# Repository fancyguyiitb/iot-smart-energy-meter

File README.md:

<!-- DON'T MODIFY ANYTHING ABOVE -->
<!-- Modify from here -->

## Run it locally (no hardware needed)

The whole system runs on one machine. A **virtual meter board** stands in for the ADE9000 chip, the relays and the house wiring. The unmodified firmware talks to it through a hardware-abstraction layer.

```bash
python -m venv .venv
.venv/Scripts/activate            # Windows  (macOS/Linux: source .venv/bin/activate)
pip install -r requirements-dev.txt

python scripts/run_local.py       # add --gui for the meter's touchscreen UI
```

| Open | What it is |
|---|---|
| http://127.0.0.1:8000/app/ | Web app: live readings, energy use, analysis, power quality, remote control |
| http://127.0.0.1:9000/ | Virtual board: switch appliances, inject sags/outages/loose neutral/solar export, watch relays and ground truth |
| http://127.0.0.1:8000/docs | API reference |

On first start the launcher prints a one-time sign-up link that registers the meter to a new account. Run `python src/RPi/claim.py` for a fresh one.

```bash
python scripts/run_tests.py       # unit + regression tests (firmware and server)
python scripts/e2e_check.py       # end-to-end checks against the running stack
```

### How it fits together

```
 Virtual board (src/VirtualDevice)          Firmware (src/RPi)                    Server (src/Server)          Web app (src/WebApp)
 physics: grid, loads, faults   <-SPI-  api.py      sampler -> SQLite (WAL)    sync.py --HTTPS batches-->  /api/write-data
 emulated ADE9000 registers             sync.py     store-and-forward                                       SQLite (local) | InfluxDB (cloud)
 relay contacts on GPIO 17/27/22 <-GPIO- relay.py   <---------- WebSocket (device key) ------------>  /ws  <- /remote-control <- browser
                                        failure_log.py, app.py (Tk touchscreen)                         /auth, /api, /analytics -> browser
```

On the real Pi, set `VOLTIX_HAL=hardware` in `src/RPi/device.env` and the same firmware uses `spidev` and `RPi.GPIO`.

### Repository layout

| Path | Contents |
|---|---|
| `src/RPi/` | Meter firmware: sampler, sync, relay control, failure logger, touchscreen GUI, ADE9000 driver, `hal/` (real or virtual hardware) |
| `src/VirtualDevice/` | Virtual meter board: physical model, register-level ADE9000 emulation, control panel |
| `src/Server/` | FastAPI backend: auth, ingest, analytics, device WebSocket, `storage/` (SQLite or InfluxDB), `manage.py` |
| `src/WebApp/` | Browser client (reference client while the Flutter source is missing) |
| `src/Application/` | Flutter project scaffold (the Dart `lib/` was lost to a `.gitignore` rule, now fixed) |
| `scripts/` | `run_local.py`, `run_tests.py`, `e2e_check.py` |
| `tests/` | Firmware and server regression tests |
| `docs/BUGFIXES.md` | Open bugs, known limitations, and the feature backlog |
| `deploy/` | InfluxDB compose file for trying the cloud storage backend |
| `pcb/`, `3d_models/`, `reports/`, `others/`, `bom.xls` | Hardware design files and project reports |

---

# Project Overview

### Project Name: [IOT Enabled 3-Phase Power Quality and Energy Meter]()

### Team Number: [TUE-17]()

### Team Members

- [Saurabh Kumar](https://www.github.com/srbh001)
- [Aryan Tamboli](https://www.github.com/Aryan-Tamboli)
- [Ayush Gaur](https://www.github.com/gaurkama)
- [Cherish Jain](https://www.github.com/CJain2004)
- [Sarthak Niranjan](https://www.github.com/fancyguyiitb)

### Problem Statement and Solution

We developed an IoT-based 3-phase smart energy meter that enables users to monitor power parameters, analyze power quality, and remotely control the power supply. The system supports real-time data logging, mobile access, and predictive maintenance via harmonics analysis.  
For setup and usage instructions, refer to [Manual.md](Manual.md)..

#### Team & Contributions

Our team of 5 worked collaboratively across various components:

- PCB design and hardware integration for accurate signal acquisition
- App development for Android with real-time graphs and analytics
- Server-side APIs and cloud storage for historical data access
- GUI and control functionalities on Raspberry Pi
- Relay-based remote disconnection of supply

#### Key Learnings & Achievements

- Practical experience in embedded systems, IoT, and full-stack development
- Developed a complete system from hardware to cloud and mobile
- Built scalable architecture and an intuitive UI for energy monitoring

## 1. Source Code

### Application/

Flutter frontend for real-time monitoring and control. Contains Dart UI code (`lib/`), assets, platform-specific code, and Flutter config files.

### RPi/

Python scripts for data collection from ADE9000, local caching via SQLite, device control, syncing, and status tracking.

### Server/

FastAPI backend for authentication, data ingestion (InfluxDB), analytics, and WebSocket command handling. Includes API routes, config, and docs.

---

## Learning from Mistakes

### 1. UI Lag Due to Excessive Local Storage Data on Raspberry Pi

**Problem:**  
We encountered significant UI lag on the Raspberry Pi when the local storage accumulated large volumes of data. This led to delayed response times, particularly while switching between tabs, resulting in a poor user experience.

**Solution Implemented:**

- **Data Limitation:** We limited local data storage to only one day's worth of energy data to prevent database bloat and ensure smoother real-time operations.
- **Historical Data Handling:** For the "History" tab, we retained only a single representative energy data point from the previous day. This allowed for historical trend analysis with minimal storage overhead.
- **Improved UI Feedback:** A loading screen was introduced when switching tabs to:
  - Indicate the system is processing,
  - Discourage excessive button tapping,
  - Improve overall user satisfaction and interface intuitiveness.

**Outcome:**  
The optimizations resulted in a significantly more responsive and user-friendly interface with better resource management on the Raspberry Pi.

---

### 2. Power Backup System Failure

**Problem:**  
The power backup system failed to operate as intended during initial testing. Despite proper wiring and configuration, the battery did not charge, leading to a complete failure of backup functionality during power outages.

**Diagnosis and Root Cause:**  
After thorough inspection, we discovered that enclosing the circuitry between two tightly fitted acrylic sheets had introduced mechanical stress. This stress likely caused certain solder joints or connectors to either loosen or become overly compressed, ultimately disrupting the battery charging pathway.

**Solution Implemented:**

- **Mechanical Redesign:** We removed one of the acrylic sheets from the enclosure to relieve the internal stress and allow for natural ventilation and movement.
- **Post-Modification Testing:** After this adjustment, the charging system began functioning correctly, indicating that the issue was indeed related to physical strain affecting circuit integrity.

**Outcome:**  
Since this mechanical modification, the backup system has consistently charged without failure. This incident highlighted the critical importance of allowing tolerance for mechanical flexibility in compact hardware designs, especially when working with sensitive analog and power electronics.

---

## Future Scope

To further enhance the system’s functionality, usability, and sustainability, future contributors can explore the following improvements:

### 1. Sound Alerts for Power Failure

Implementing audio alerts during power failures can significantly improve user responsiveness and system awareness. Key aspects of this feature include:

- **Immediate Notifications:** Sound alerts ensure that users are informed of outages even when they are not actively monitoring the screen.
- **Severity-based Tones:** Different tones can indicate varying levels of urgency, such as battery low, power cut, or system reboot.
- **Remote Deployment Advantage:** Especially beneficial for systems installed in remote or unattended locations.

### 2. Integration with Solar Energy

Adding solar energy support can make the system more eco-friendly and independent of the grid. Potential features include:

- **Real-Time Monitoring:** Track solar power input and battery charge levels live.
- **Smart Source Switching:** Automatically switch between grid and solar based on availability and efficiency.
- **Analytics and Optimization:** Log and compare energy generation versus consumption to inform sustainable usage patterns.

**Impact:**  
These enhancements will improve system reliability, promote green energy adoption, and make the solution more adaptable to diverse deployment scenarios including smart homes, rural areas, and energy-conscious environments.

---

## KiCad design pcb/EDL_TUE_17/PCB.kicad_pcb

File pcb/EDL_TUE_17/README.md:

# IoT Enabled 3-Phase Energy Meter - PCB Design

This folder contains the KiCAD schematic and PCB design files for the **IoT Enabled 3-Phase Energy Meter** project. The energy meter is designed to measure and monitor three-phase electrical parameters and transmit data to a Raspberry Pi for further processing and control.

## Folder Structure

```
.
├── PCB.kicad_sch
├── Current_Sense_Block.kicad_sch
├── Voltage_Sense_Block.kicad_sch
├── Relay_Drive.kicad_sch
└── energy_meter_pcb.kicad_pcb
```

## Overview

The PCB integrates multiple blocks to accurately measure electrical parameters using the ADE9000 IC, isolate the high-voltage and low-voltage domains, and interface with a Raspberry Pi for data communication and relay control.

---

## Block Description

### Voltage and Current Sensing Blocks

- **Input:**
  - 3 Phase Voltages (Line to Neutral) and Neutral connected to the **Voltage Sensing Block**
  - Current Transformers (CTs) connected to the **Current Sensing Block**
- **Function:**  
  These blocks scale down voltage and current to ranges compatible with the **ADE9000** IC.

### ADE9000 Measurement IC

- Measures:
  - Voltage, Current, Power, Energy, THD, etc.
- Communicates with Raspberry Pi using **SPI interface**
- Receives scaled-down signals from the sensing blocks

### Isolation Block

- **ICs Used:**
  - `ADUM6404` – Power and signal isolation
  - `ADUM4151` – SPI digital isolation
- Provides isolation between the high-voltage side (connected to mains) and low-voltage control logic (Raspberry Pi)

### Relay Control Block

- Controls 3 individual relays for 3-phase control
- Each relay is driven using a **TIP41C** NPN transistor
- Controlled through Raspberry Pi GPIO pins

### Power Supply

- **5V** supplied from RPI\*\*
- Appropriate headers and connectors included on the PCB for all connections

---

## Status

- PCB designed and tested
- All blocks working as intended

---

## Tools Used

- **KiCAD** for schematic and PCB design

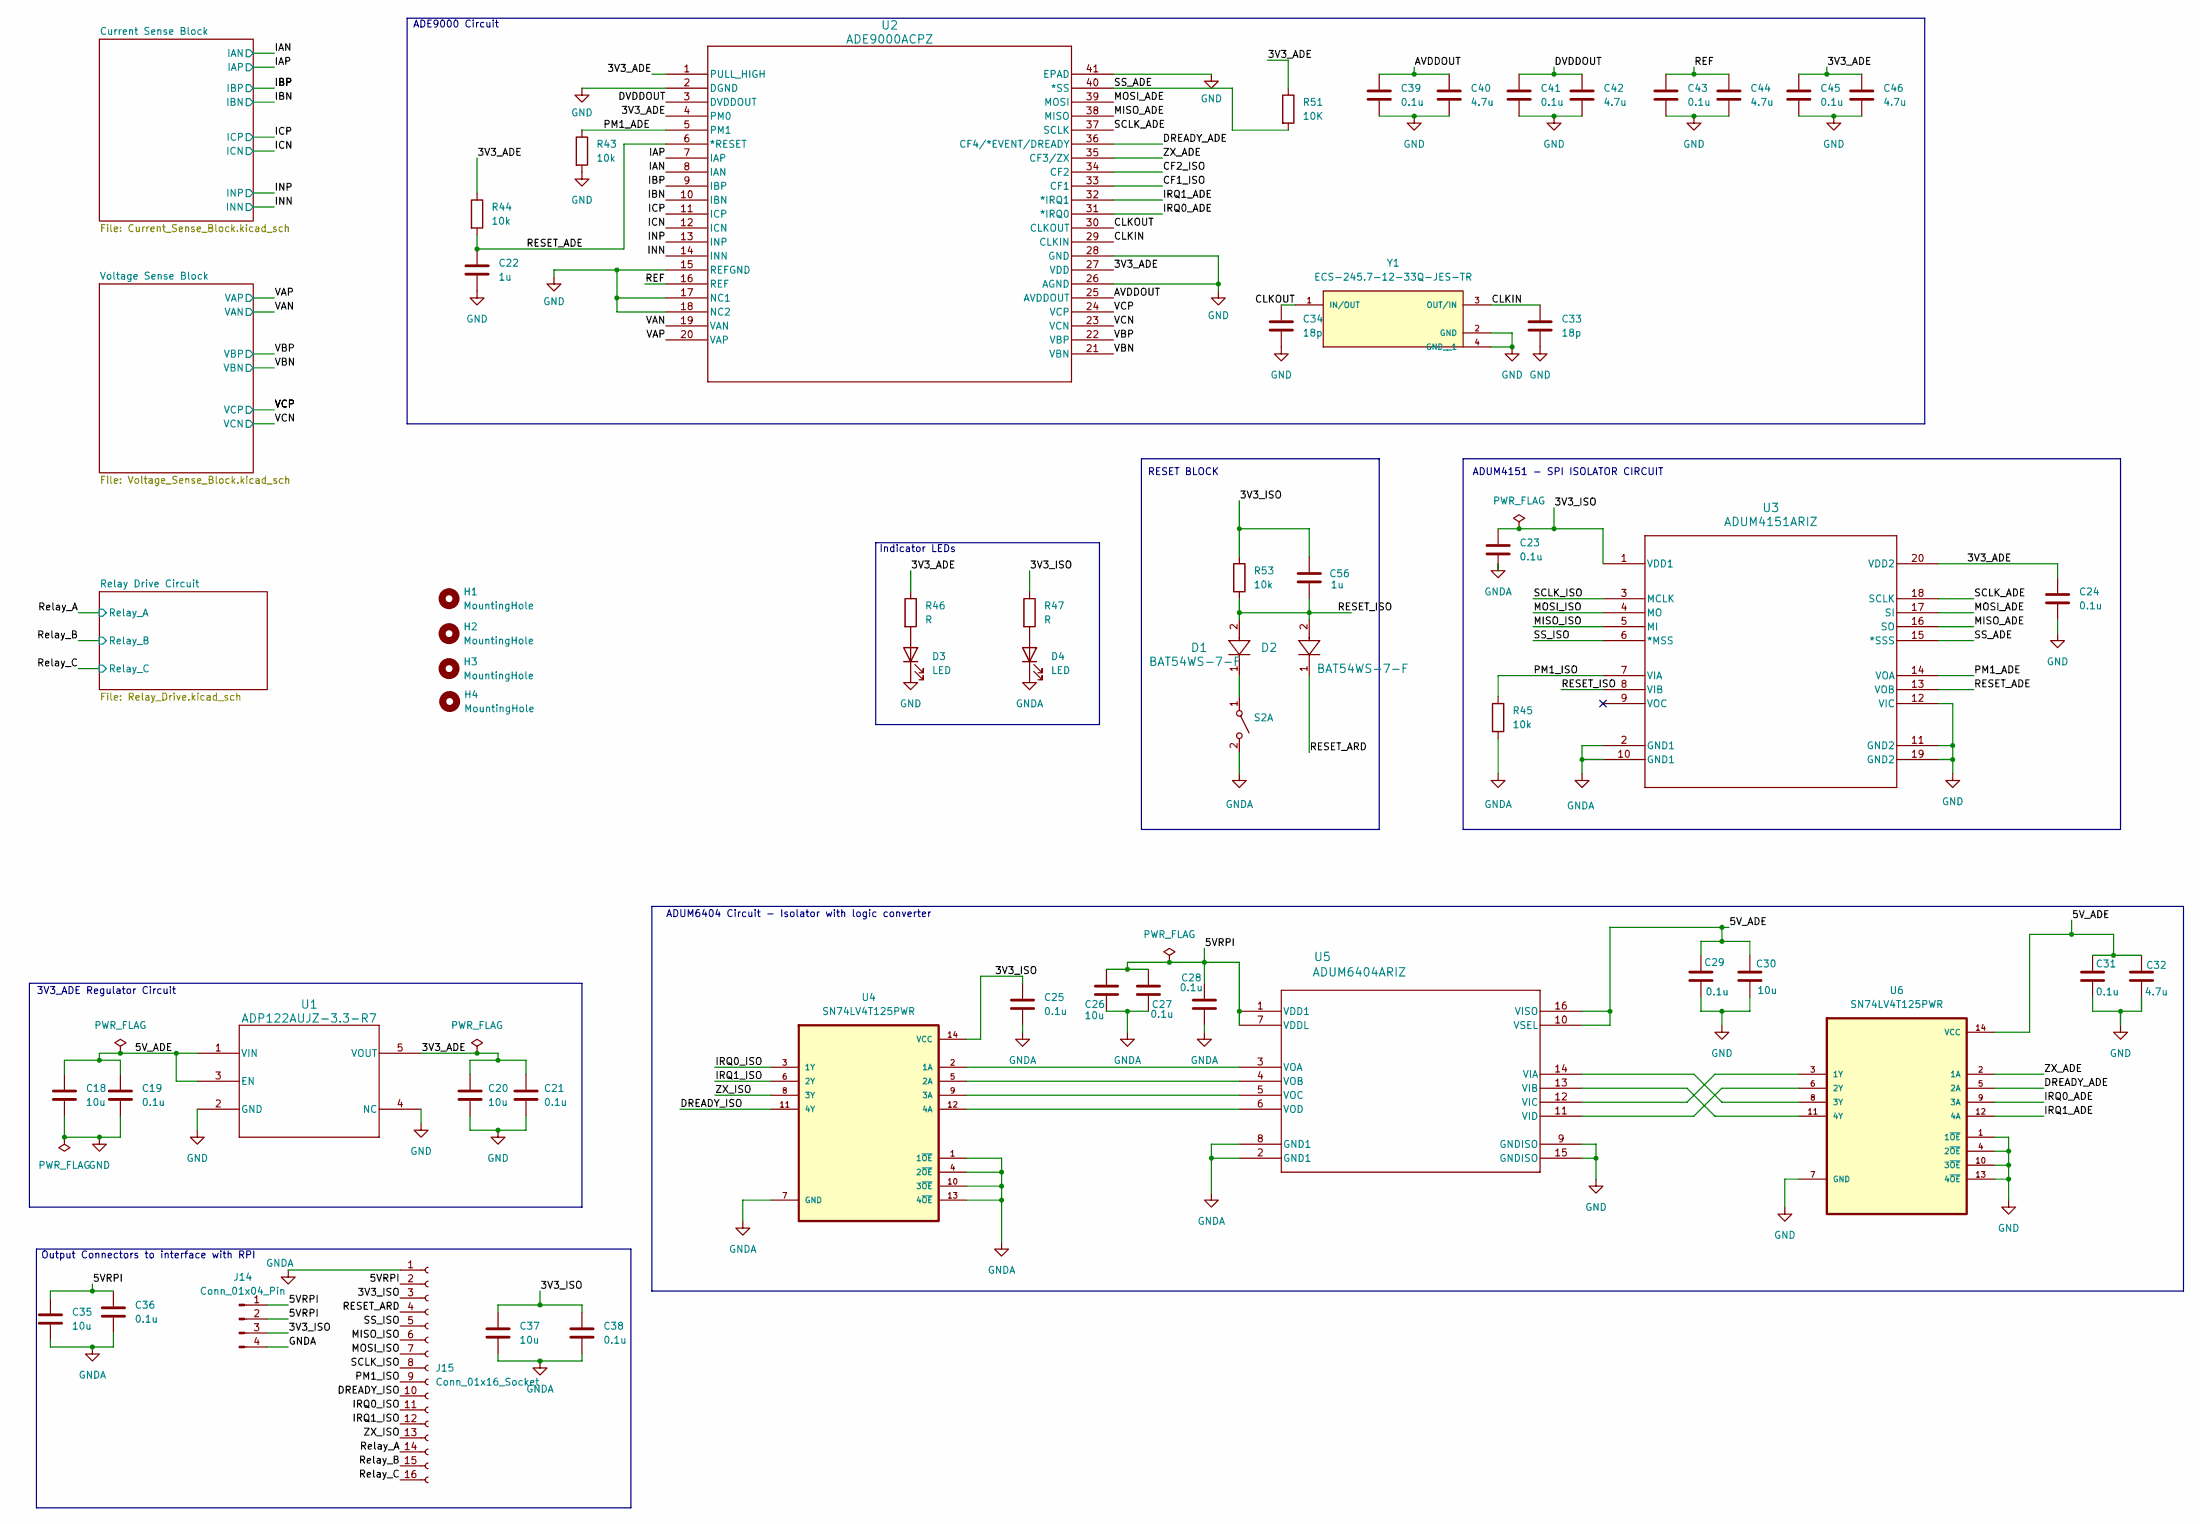
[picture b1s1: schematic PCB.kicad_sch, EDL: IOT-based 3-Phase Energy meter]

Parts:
C18, C20, C26, C30, C35, C37: 10u; C_0805_2012Metric_Pad1.18x1.45mm_HandSolder
C19, C21, C23, C24, C25, C27, C28, C29, C31, C36, C38, C39, C41, C43, C45: 0.1u; C_0603_1608Metric_Pad1.08x0.95mm_HandSolder
C22, C56: 1u; C_0603_1608Metric_Pad1.08x0.95mm_HandSolder
C32, C40, C42, C44, C46: 4.7u; C_0805_2012Metric_Pad1.18x1.45mm_HandSolder
C33, C34: 18p; C_0402_1005Metric_Pad0.74x0.62mm_HandSolder
D1, D2: BAT54WS-7-F; SOD323_DIO
D3, D4: LED; LED_1206_3216Metric_Pad1.42x1.75mm_HandSolder
H1, H2, H3, H4: MountingHole; MountingHole_3.2mm_M3
J14: Conn_01x04_Pin; PinHeader_1x04_P2.54mm_Vertical
J15: Conn_01x16_Socket; PinSocket_1x16_P2.54mm_Vertical
R43, R44, R45, R53: 10k; R_0805_2012Metric_Pad1.20x1.40mm_HandSolder
R46, R47: R; R_1206_3216Metric_Pad1.30x1.75mm_HandSolder
R51: 10K; R_0805_2012Metric_Pad1.20x1.40mm_HandSolder
S2: SW_Push_2P1T_Toggle_CK_PVA1xxH4xxxxxxV2
U1: ADP122AUJZ-3.3-R7; UJ_5_ADI
U2: ADE9000ACPZ; ADE9000ACPZ_ADI
U3: ADUM4151ARIZ; RI_20_1_ADI
U4, U6: SN74LV4T125PWR; SOP65P640X120-14N
U5: ADUM6404ARIZ; RI_16_1_ADI
Y1: ECS-245.7-12-33Q-JES-TR; XTAL_ECS-245.7-12-33Q-JES-TR

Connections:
/3V3_ADE: C20.1, C21.1, C24.1, C45.1, C46.1, R44.1, R46.1, R51.1, U1.5 (VOUT), U2.1 (PULL_HIGH), U2.4 (PM0), U2.27 (VDD), U3.20 (VDD2)
/3V3_ISO: C23.1, C25.1, C37.1, C38.1, C56.1, J14.3, J15.3, R47.1, R53.1, U3.1 (VDD1), U4.14 (VCC)
/5VRPI: C26.1, C27.1, C28.1, C35.1, C36.1, J14.1, J14.2, J15.2, U5.1 (VDD1), U5.7 (VDDL)
/5V_ADE: C18.1, C19.1, C29.1, C30.1, C31.1, C32.1, U1.1 (VIN), U1.3 (EN), U5.10 (VSEL), U5.16 (VISO), U6.14 (VCC)
/AVDDOUT: C39.1, C40.1, U2.25 (AVDDOUT)
/CF1_ISO: U2.33 (CF1)
/CF2_ISO: U2.34 (CF2)
/CLKIN: C33.1, U2.29 (CLKIN), Y1.3 (OUT/IN)
/CLKOUT: C34.1, U2.30 (CLKOUT), Y1.1 (IN/OUT)
/DREADY_ADE: U2.36 (CF4/*EVENT/DREADY), U6.5 (2A)
/DREADY_ISO: J15.10, U4.11 (4Y)
/DVDDOUT: C41.1, C42.1, U2.3 (DVDDOUT)
/IAN: U2.8 (IAN); also elsewhere on the board
/IAP: U2.7 (IAP); also elsewhere on the board
/IBN: U2.10 (IBN); also elsewhere on the board
/IBP: U2.9 (IBP); also elsewhere on the board
/ICN: U2.12 (ICN); also elsewhere on the board
/ICP: U2.11 (ICP); also elsewhere on the board
/INN: U2.14 (INN); also elsewhere on the board
/INP: U2.13 (INP); also elsewhere on the board
/IRQ0_ADE: U2.31 (*IRQ0), U6.9 (3A)
/IRQ0_ISO: J15.11, U4.3 (1Y)
/IRQ1_ADE: U2.32 (*IRQ1), U6.12 (4A)
/IRQ1_ISO: J15.12, U4.6 (2Y)
/MISO_ADE: U2.38 (MISO), U3.16 (SO)
/MISO_ISO: J15.6, U3.5 (MI)
/MOSI_ADE: U2.39 (MOSI), U3.17 (SI)
/MOSI_ISO: J15.7, U3.4 (MO)
/PM1_ADE: R43.1, U2.5 (PM1), U3.14 (VOA)
/PM1_ISO: J15.9, R45.1, U3.7 (VIA)
/REF: C43.1, C44.1, U2.16 (REF)
/RESET_ADE: C22.1, R44.2, U2.6 (*RESET), U3.13 (VOB)
/RESET_ARD: D2.1, J15.4
/RESET_ISO: C56.2, D1.2, D2.2, R53.2, U3.8 (VIB)
/Relay_A: J15.14; also elsewhere on the board
/Relay_B: J15.15; also elsewhere on the board
/Relay_C: J15.16; also elsewhere on the board
/SCLK_ADE: U2.37 (SCLK), U3.18 (SCLK)
/SCLK_ISO: J15.8, U3.3 (MCLK)
/SS_ADE: R51.2, U2.40 (*SS), U3.15 (*SSS)
/SS_ISO: J15.5, U3.6 (*MSS)
/VAN: U2.19 (VAN); also elsewhere on the board
/VAP: U2.20 (VAP); also elsewhere on the board
/VBN: U2.21 (VBN); also elsewhere on the board
/VBP: U2.22 (VBP); also elsewhere on the board
/VCN: U2.23 (VCN); also elsewhere on the board
/VCP: U2.24 (VCP); also elsewhere on the board
/ZX_ADE: U2.35 (CF3/ZX), U6.2 (1A)
/ZX_ISO: J15.13, U4.8 (3Y)
GND: C18.2, C19.2, C20.2, C21.2, C22.2, C24.2, C29.2, C30.2, C31.2, C32.2, C33.2, C34.2, C39.2, C40.2, C41.2, C42.2, C43.2, C44.2, C45.2, C46.2, D3.1 (K), R43.2, U1.2 (GND), U1.4 (NC), U2.2 (DGND), U2.15 (REFGND), U2.17 (NC1), U2.18 (NC2), U2.26 (AGND), U2.28 (GND), U2.41 (EPAD), U3.11 (GND2), U3.12 (VIC), U3.19 (GND2), U5.9 (GNDISO), U5.15 (GNDISO), U6.1 (1~OE), U6.4 (2~OE), U6.7 (GND), U6.10 (3~OE), U6.13 (4~OE), Y1.2 (GND), Y1.4 (GND__1); also elsewhere on the board
GNDA: C23.2, C25.2, C26.2, C27.2, C28.2, C35.2, C36.2, C37.2, C38.2, D4.1 (K), J14.4, J15.1, R45.2, S2.2 (B), U3.2 (GND1), U3.10 (GND1), U4.1 (1~OE), U4.4 (2~OE), U4.7 (GND), U4.10 (3~OE), U4.13 (4~OE), U5.2 (GND1), U5.8 (GND1); also elsewhere on the board
unnamed: D3.2 (A), R46.2
unnamed: D4.2 (A), R47.2
unnamed: D1.1, S2.1 (A)
unnamed: U4.2 (1A), U5.3 (VOA)
unnamed: U4.5 (2A), U5.4 (VOB)
unnamed: U4.9 (3A), U5.5 (VOC)
unnamed: U4.12 (4A), U5.6 (VOD)
unnamed: U5.14 (VIA), U6.8 (3Y)
unnamed: U5.13 (VIB), U6.11 (4Y)
unnamed: U5.12 (VIC), U6.3 (1Y)
unnamed: U5.11 (VID), U6.6 (2Y)

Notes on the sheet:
RESET BLOCK
Output Connectors to interface with RPI
ADUM4151 - SPI ISOLATOR CIRCUIT
Indicator LEDs
ADUM6404 Circuit - Isolator with logic converter
ADE9000 Circuit
3V3_ADE Regulator Circuit

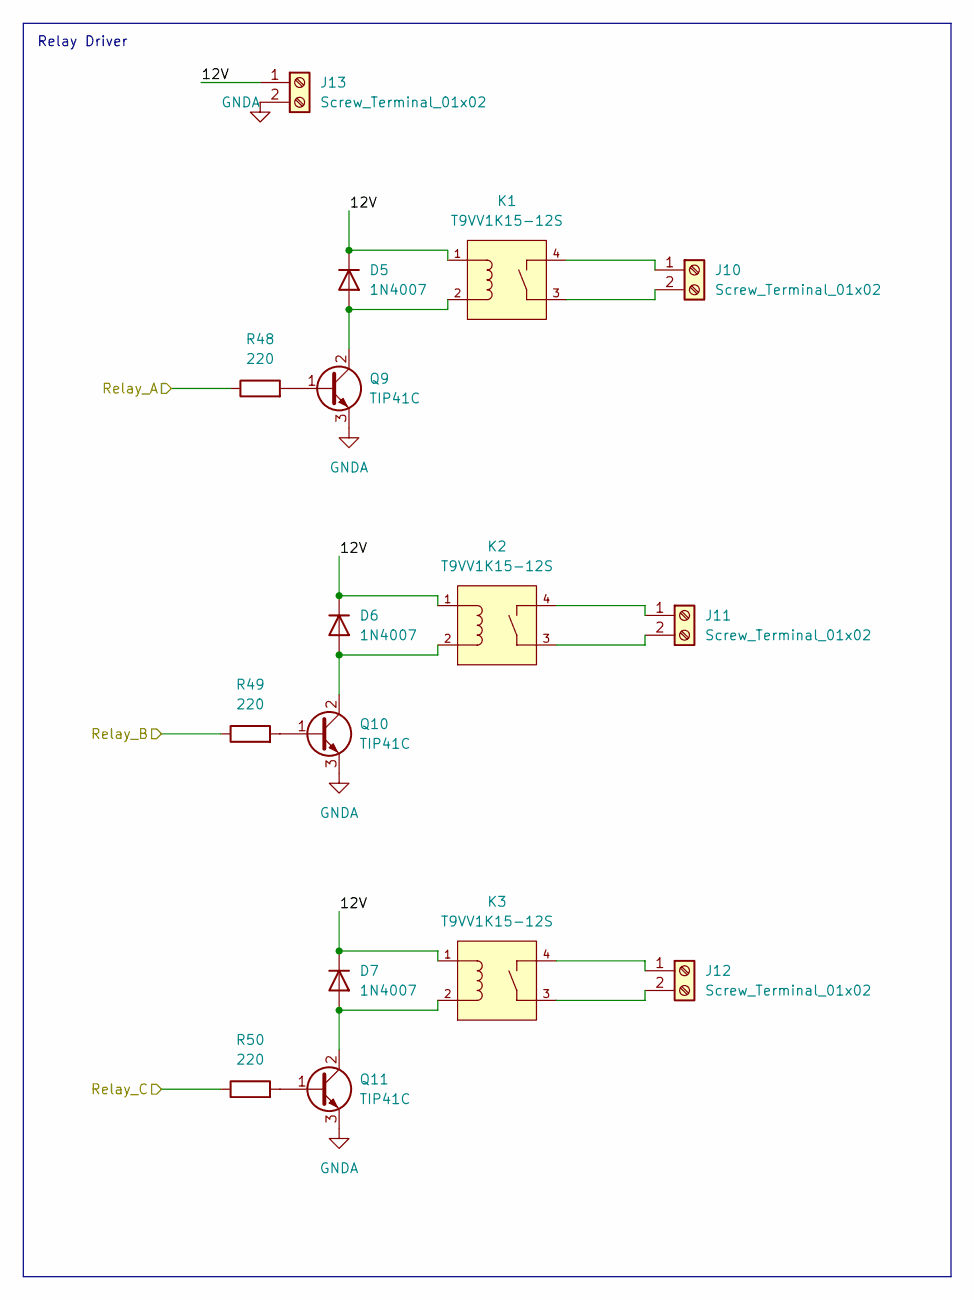
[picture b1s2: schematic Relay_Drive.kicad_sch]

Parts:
D5, D6, D7: 1N4007; D_DO-41_SOD81_P10.16mm_Horizontal
J10, J11, J12, J13: Screw_Terminal_01x02; TerminalBlock_Phoenix_PT-1,5-2-5.0-H_1x02_P5.00mm_Horizontal
K1, K2, K3: T9VV1K15-12S; RELAY_T9VV1K15-12S
Q9, Q10, Q11: TIP41C; TO-220-3_Vertical
R48, R49, R50: 220; R_1206_3216Metric_Pad1.30x1.75mm_HandSolder

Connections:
/Relay Drive Circuit/12V: D5.1 (K), D6.1 (K), D7.1 (K), J13.1, K1.1, K2.1, K3.1
/Relay_A: R48.1; also elsewhere on the board
/Relay_B: R49.1; also elsewhere on the board
/Relay_C: R50.1; also elsewhere on the board
GNDA: J13.2, Q9.3 (E), Q10.3 (E), Q11.3 (E); also elsewhere on the board
unnamed: D5.2 (A), K1.2, Q9.2 (C)
unnamed: D6.2 (A), K2.2, Q10.2 (C)
unnamed: D7.2 (A), K3.2, Q11.2 (C)
unnamed: J10.1, K1.4
unnamed: J10.2, K1.3
unnamed: J11.1, K2.4
unnamed: J11.2, K2.3
unnamed: J12.1, K3.4
unnamed: J12.2, K3.3
unnamed: Q9.1 (B), R48.2
unnamed: Q10.1 (B), R49.2
unnamed: Q11.1 (B), R50.2

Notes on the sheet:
Relay Driver

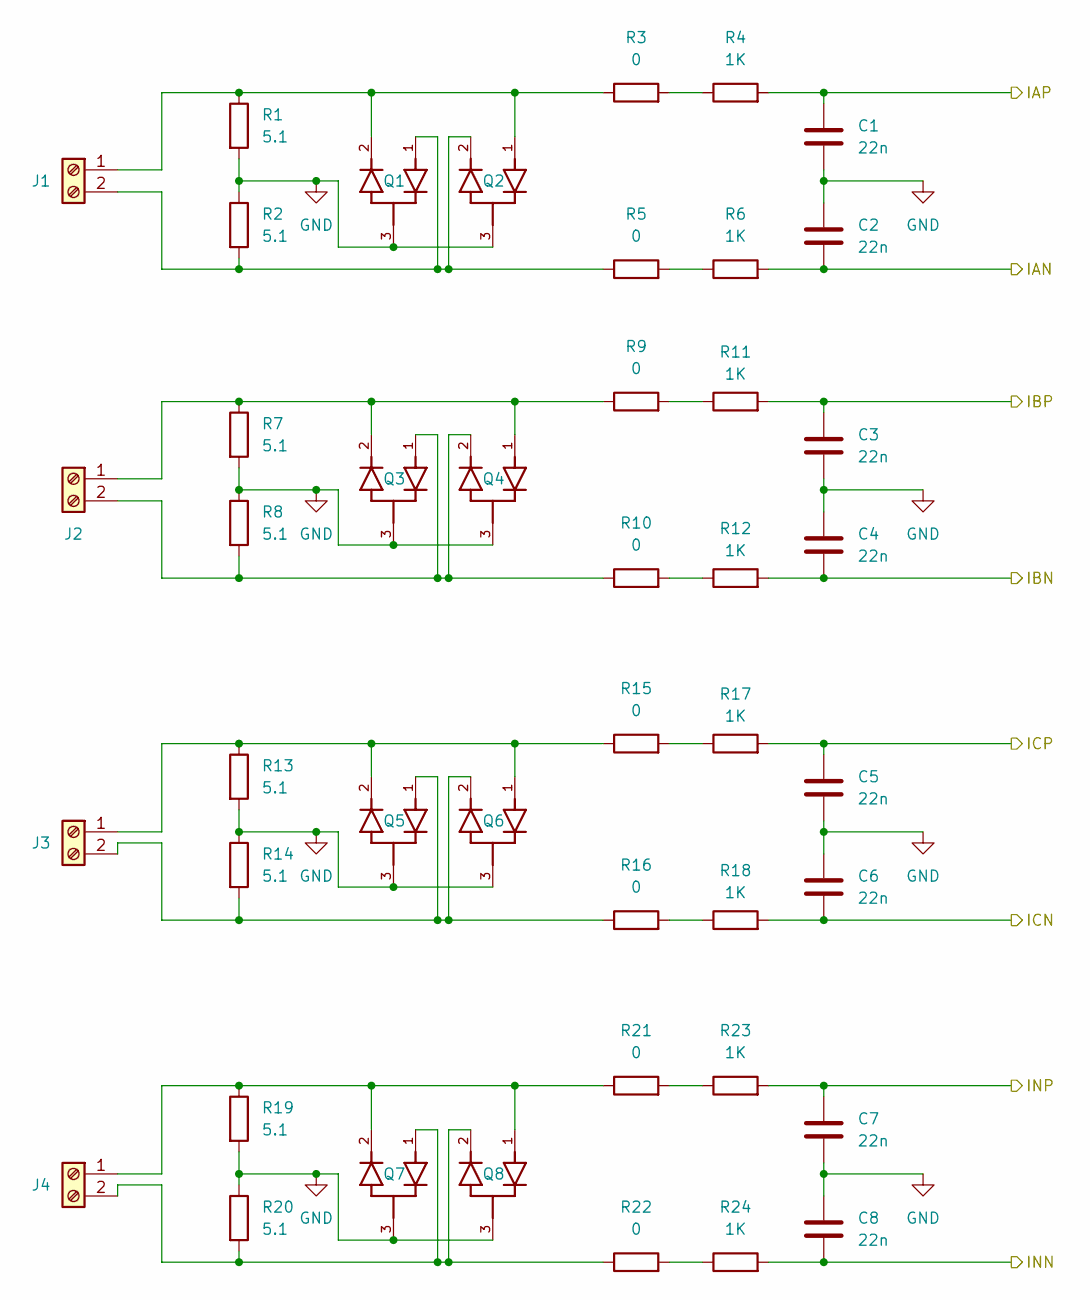
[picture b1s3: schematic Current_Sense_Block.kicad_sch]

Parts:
C1, C2, C3, C4, C5, C6, C7, C8: 22n; C_0805_2012Metric_Pad1.18x1.45mm_HandSolder
J1, J2, J3, J4: Screw_Terminal_01x02; TerminalBlock_Phoenix_PT-1,5-2-5.0-H_1x02_P5.00mm_Horizontal
Q1, Q2, Q3, Q4, Q5, Q6, Q7, Q8: MMBD4148SE_RFG; SOT95P237X112-3N; PARTREV E2001
R1, R2, R7, R8, R13, R14, R19, R20: 5.1; R_0805_2012Metric_Pad1.20x1.40mm_HandSolder
R3, R5, R9, R10, R15, R16, R21, R22: 0; R_0603_1608Metric_Pad0.98x0.95mm_HandSolder
R4, R6, R11, R12, R17, R18, R23, R24: 1K; R_0805_2012Metric_Pad1.20x1.40mm_HandSolder

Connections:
/IAN: C2.2, R6.2; also elsewhere on the board
/IAP: C1.1, R4.2; also elsewhere on the board
/IBN: C4.2, R12.2; also elsewhere on the board
/IBP: C3.1, R11.2; also elsewhere on the board
/ICN: C6.2, R18.2; also elsewhere on the board
/ICP: C5.1, R17.2; also elsewhere on the board
/INN: C8.2, R24.2; also elsewhere on the board
/INP: C7.1, R23.2; also elsewhere on the board
GND: C1.2, C2.1, C3.2, C4.1, C5.2, C6.1, C7.2, C8.1, Q1.3, Q2.3, Q3.3, Q4.3, Q5.3, Q6.3, Q7.3, Q8.3, R1.2, R2.1, R7.2, R8.1, R13.2, R14.1, R19.2, R20.1; also elsewhere on the board
unnamed: J1.1, Q1.2, Q2.1, R1.1, R3.1
unnamed: J1.2, Q1.1, Q2.2, R2.2, R5.1
unnamed: J2.1, Q3.2, Q4.1, R7.1, R9.1
unnamed: J2.2, Q3.1, Q4.2, R8.2, R10.1
unnamed: J3.1, Q5.2, Q6.1, R13.1, R15.1
unnamed: J3.2, Q5.1, Q6.2, R14.2, R16.1
unnamed: J4.1, Q7.2, Q8.1, R19.1, R21.1
unnamed: J4.2, Q7.1, Q8.2, R20.2, R22.1
unnamed: R3.2, R4.1
unnamed: R5.2, R6.1
unnamed: R10.2, R12.1
unnamed: R9.2, R11.1
unnamed: R15.2, R17.1
unnamed: R16.2, R18.1
unnamed: R21.2, R23.1
unnamed: R22.2, R24.1

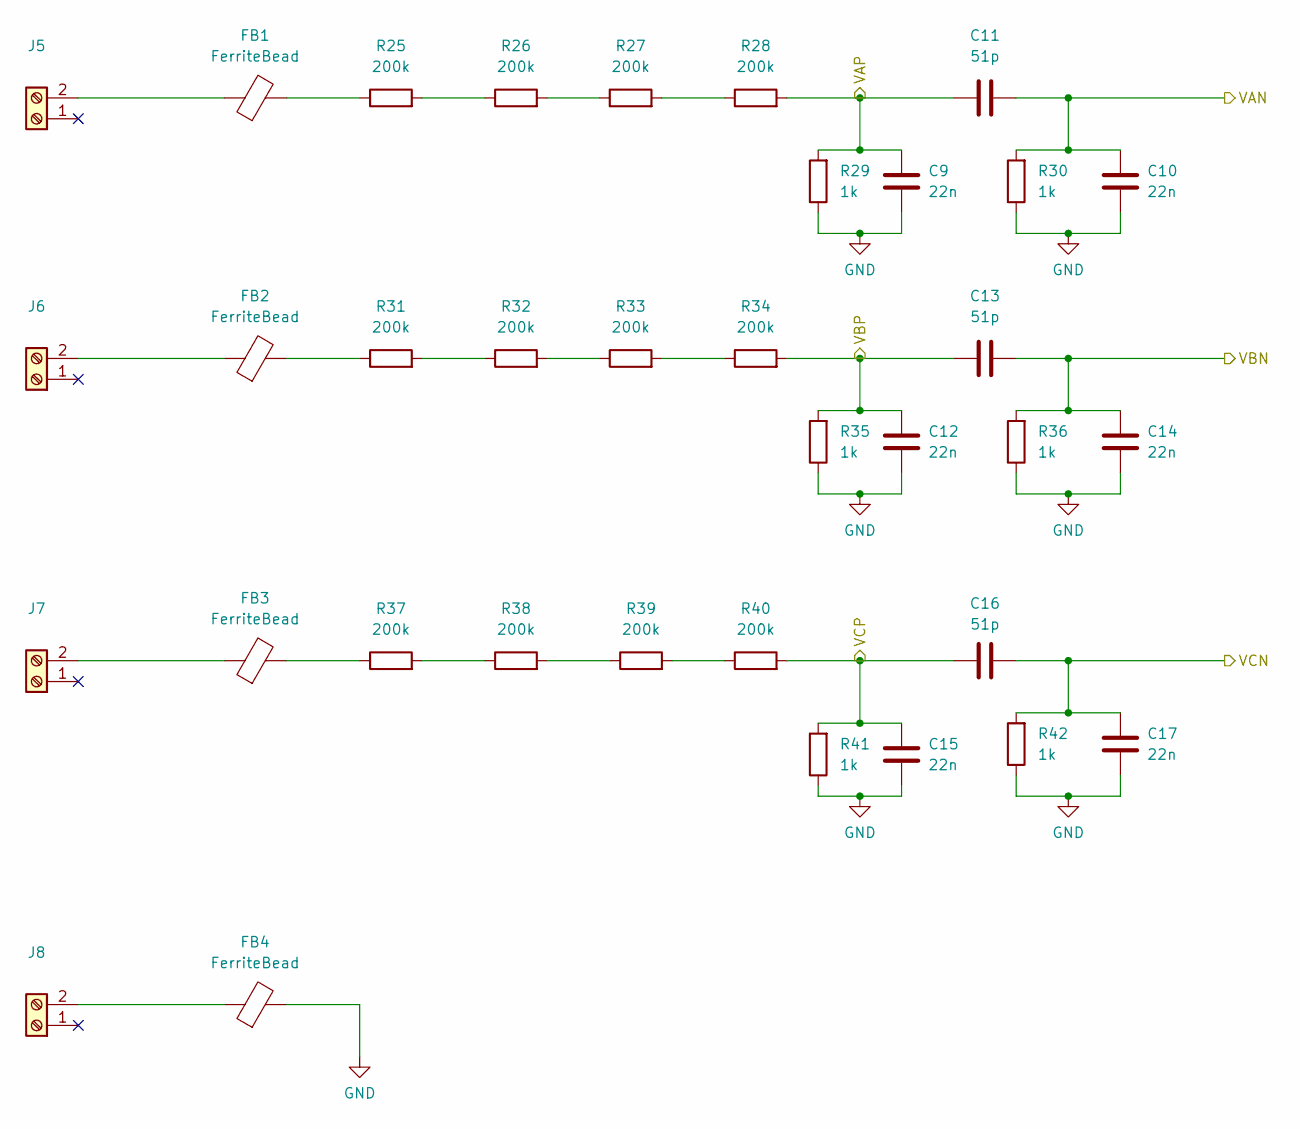
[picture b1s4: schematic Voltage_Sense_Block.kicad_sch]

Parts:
C9, C10, C12, C14, C15, C17: 22n; C_0805_2012Metric_Pad1.18x1.45mm_HandSolder
C11, C13, C16: 51p; C_0402_1005Metric_Pad0.74x0.62mm_HandSolder
FB1, FB2, FB3, FB4: FerriteBead; L_0805_2012Metric_Pad1.15x1.40mm_HandSolder
J5, J6, J7, J8: Screw_Terminal_01x02; TerminalBlock_Phoenix_PT-1,5-2-5.0-H_1x02_P5.00mm_Horizontal
R25, R26, R27, R28, R31, R32, R33, R34, R37, R38, R39, R40: 200k; R_1206_3216Metric_Pad1.30x1.75mm_HandSolder
R29, R30, R35, R36, R41, R42: 1k; R_0805_2012Metric_Pad1.20x1.40mm_HandSolder

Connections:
/VAN: C10.1, C11.2, R30.2; also elsewhere on the board
/VAP: C9.1, C11.1, R28.2, R29.2; also elsewhere on the board
/VBN: C13.2, C14.1, R36.2; also elsewhere on the board
/VBP: C12.1, C13.1, R34.2, R35.2; also elsewhere on the board
/VCN: C16.2, C17.1, R42.2; also elsewhere on the board
/VCP: C15.1, C16.1, R40.2, R41.2; also elsewhere on the board
GND: C9.2, C10.2, C12.2, C14.2, C15.2, C17.2, FB4.2, R29.1, R30.1, R35.1, R36.1, R41.1, R42.1; also elsewhere on the board
unnamed: FB1.2, R25.1
unnamed: FB2.2, R31.1
unnamed: FB3.2, R37.1
unnamed: FB1.1, J5.2
unnamed: FB2.1, J6.2
unnamed: FB3.1, J7.2
unnamed: FB4.1, J8.2
unnamed: R25.2, R26.1
unnamed: R26.2, R27.1
unnamed: R27.2, R28.1
unnamed: R31.2, R32.1
unnamed: R32.2, R33.1
unnamed: R33.2, R34.1
unnamed: R37.2, R38.1
unnamed: R38.2, R39.1
unnamed: R39.2, R40.1

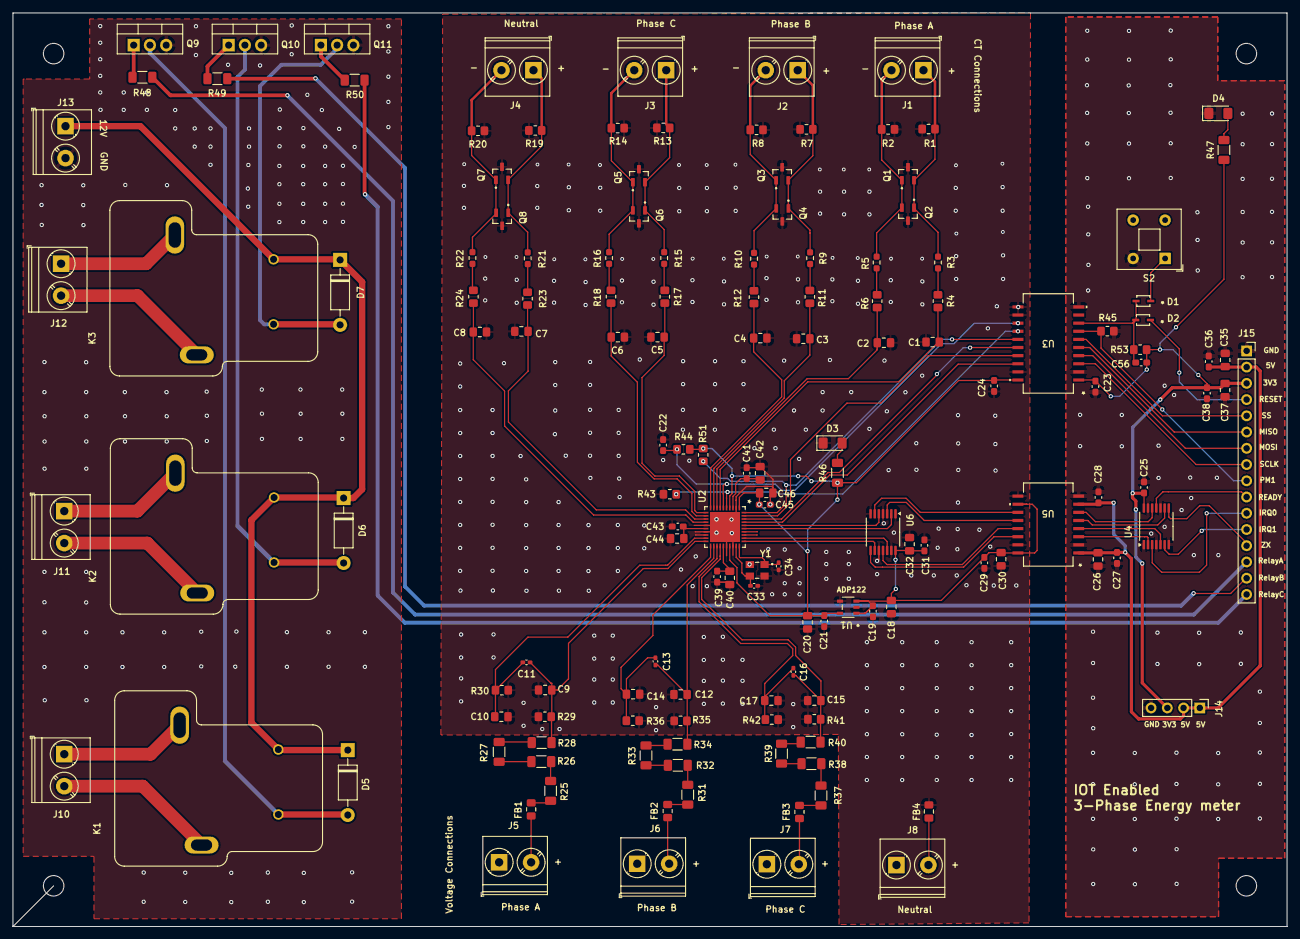
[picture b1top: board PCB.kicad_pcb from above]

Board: 2 copper layers, 199.3 x 142.9 mm, 150 parts (0 on the bottom side), 105 nets.

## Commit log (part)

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2025-04-05 Submission Guidelines Added
2025-04-05 Grading Workflow Attached
    Assignment workflow check added
2025-04-05 Submission Instructions Added
2025-04-05 README modified
2025-04-05 Submission Badge Added
2025-04-05 Badge Status changed
2025-04-08 add deadline
2025-04-09 Badge Status Update for teams
2025-04-13 Initial Commit
    Todos:
    - Fix README
    - Add BOM
2025-04-13 Add README
2025-04-13 Add bom
2025-04-13 Add others
2025-04-13 Add reports and 3d models
2025-04-15 Update REAMDE and add Manual
